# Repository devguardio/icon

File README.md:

ICON the internets RGB panel
-----------------------------

A  WIFI connected RGB panel you can directly program on your personal computer using javascript, golang, rust, C, C++, python, etc

Display stuff from afar without a cloud! The devguard carrier SDK allows direct peer to peer encrypted connection to the device over the internet.

Getting started
===============

1. Press the reset button to reset to factory settings
2. use the ESP Provision App to supply your wifi password
3. Scan the bardcode on your device to get the devguard carrier identity
4. run `carrier config auth <identity> auth add self "*"`
5. play with the example source code to display some pixels!

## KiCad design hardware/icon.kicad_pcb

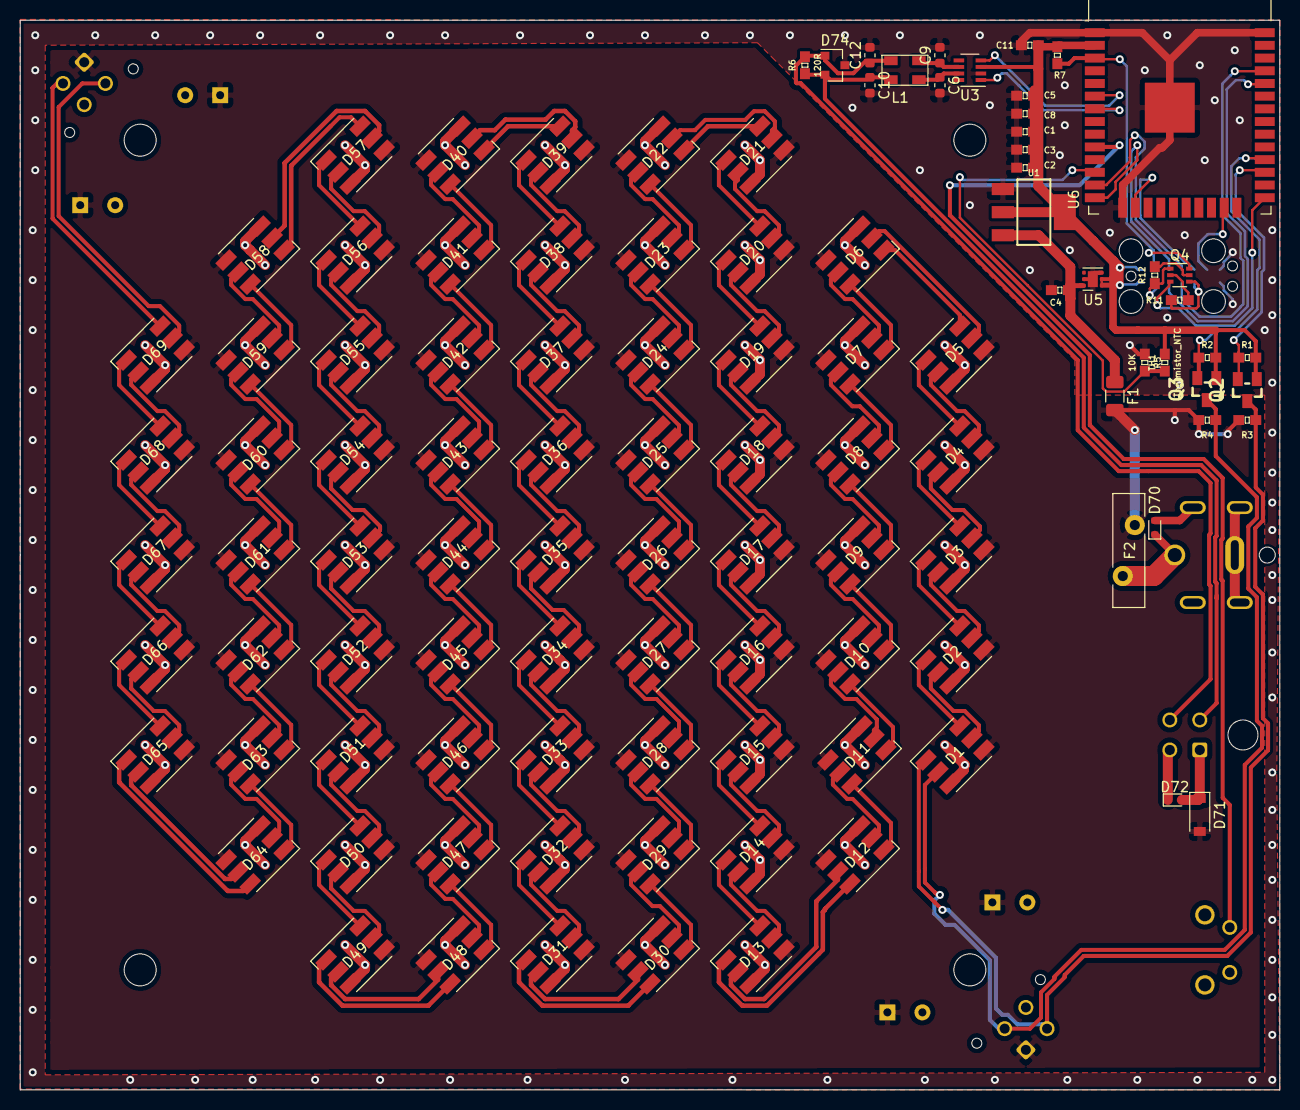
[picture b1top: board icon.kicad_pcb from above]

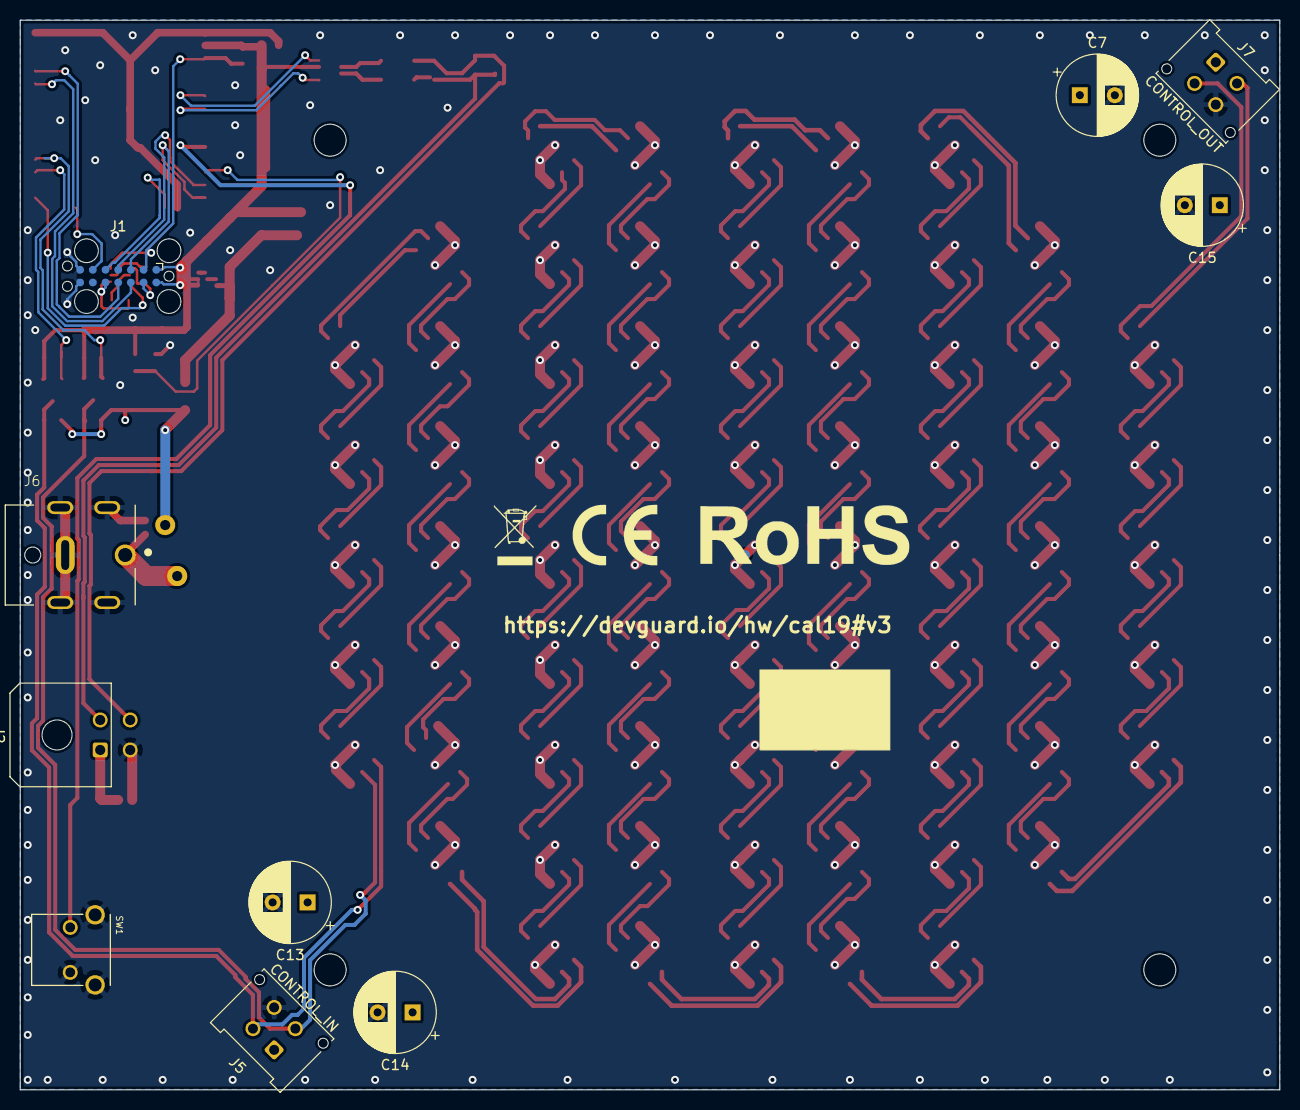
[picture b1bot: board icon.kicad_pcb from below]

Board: 2 copper layers, 126.0 x 107.0 mm, 122 parts (14 on the bottom side), 168 nets.

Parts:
C1, C2, C3, C5, C8, C11: 2.2uF; 0603
C4: 1uF; 0603
C6, C9, C10, C12: 56pf; C_0603_1608Metric
C7, C13, C14, C15: CP; CP_Radial_D8.0mm_P3.50mm
D1, D2, D3, D4, D5, D6, D7, D8, D9, D10, D11, D12, D13, D14, D15, D16, D17, D18, D19, D20, D21, D22, D23, D24, D25, D26, D27, D28, D29, D30, D31, D32, D33, D34, D35, D36, D37, D38, D39, D40, D41, D42, D43, D44, D45, D46, D47, D48, D49, D50, D51, D52, D53, D54, D55, D56, D57, D58, D59, D60, D61, D62, D63, D64, D65, D66, D67, D68, D69: APA102; LED_RGB_5050-6
D70: Transient Suppressor 7-8V clamp; D_SOD-523
D71: D_Schottky 3A; D_SOD-123
D72: Transient Suppressor; D_SOD-523
D74: SZNUP2105L; SOT-23
F1: PTC 0.5A; Fuse_1206_3216Metric
F2: 650-RGEF500; Fuse_Bourns_MF-RHT500
FID1: Fiducial; FIDUCIAL-1X2
H1, H2, H3, H4: MountingHole; MountingHole_3.2mm_M3
J1: UART; Tag-Connect_TC2070-IDC-FP_2x07_P1.27mm_Vertical
J2: Conn_02x02_Top_Bottom; Molex_Micro-Fit_3.0_43045-0400_2x02_P3.00mm_Horizontal
J5: CONTROL_IN; Molex_Micro-Fit_3.0_43045-0412_2x02_P3.00mm_Vertical
J6: PJ-082BH; CUI_PJ-082BH
J7: CONTROL_OUT; Molex_Micro-Fit_3.0_43045-0412_2x02_P3.00mm_Vertical
L1: PE-1210ACC110STS 11UH; PE-1210ACC
Q2, Q3: MOSFET-NCH-BSS138; SOT23-3
Q4: MBT3904DW1; SOT-363_SC-70-6
R1, R2, R3, R4, R5, R7, R11, R12: 10K; 0603
R6: 120R; 0603
SW1: SW_Push; SW_1825027-5
TH1: Thermistor_NTC; 0603
U1: AZ1117IH-3.3TRG; SOT223
U3: TCAN332; SOT-23-8
U5: 595-TLV76733DRVR; WSON-6-1EP_2x2mm_P0.65mm_EP1x1.6mm
U6: ESP32-WROOM-32D; ESP32-WROOM-32
X1: dummy; WEEE-Logo_4.2x6mm_SilkScreen
X2: dummy; RoHS-Logo_6mm_SilkScreen
X3: dummy; CE-Logo_8.5x6mm_SilkScreen

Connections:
5V: C7.1, C13.1, C14.1, C15.1, D1.4, D2.4, D3.4, D4.4, D5.4, D6.4, D7.4, D8.4, D9.4, D10.4, D11.4, D12.4, D13.4, D14.4, D15.4, D16.4, D17.4, D18.4, D19.4, D20.4, D21.4, D22.4, D23.4, D24.4, D25.4, D26.4, D27.4, D28.4, D29.4, D30.4, D31.4, D32.4, D33.4, D34.4, D35.4, D36.4, D37.4, D38.4, D39.4, D40.4, D41.4, D42.4, D43.4, D44.4, D45.4, D46.4, D47.4, D48.4, D49.4, D50.4, D51.4, D52.4, D53.4, D54.4, D55.4, D56.4, D57.4, D58.4, D59.4, D60.4, D61.4, D62.4, D63.4, D64.4, D65.4, D66.4, D67.4, D68.4, D69.4, D71.2, F1.2, F2.1, J5.1, J7.1, R3.2, R4.2
/c2+: C6.1, L1.2, U3.7
/c2-: C9.1, L1.1, U3.6
ADC_T: R5.2, TH1.1, U6.12
C0: D1.2, J5.3, Q3.3, R4.1
C1: D31.5, D32.2
CAN0+: C10.1, D74.2, J2.2, L1.3, R6.1
CAN0-: C12.1, D74.1, J2.4, L1.4, R6.2
CAN_RX: U3.4, U6.6
CAN_TX: U3.1, U6.7
CPU_BOOT: Q4.3, U6.25
CPU_ENABLE: J1.2, Q4.6, R7.1, U6.3
D0: D1.1, J5.2, Q2.3, R3.1
D1: D31.6, D32.1
FTDI_CTS: J1.13, Q4.1, R12.1
FTDI_DTR: J1.10, Q4.4, R11.1
FTDI_RXD: J1.11, U6.35
FTDI_TXD: J1.12, U6.34
GND: C1.2, C2.2, C3.2, C4.2, C5.2, C6.2, C7.2, C8.2, C9.2, C10.2, C11.2, C12.2, C13.2, C14.2, C15.2, D1.3, D2.3, D3.3, D4.3, D5.3, D6.3, D7.3, D8.3, D9.3, D10.3, D11.3, D12.3, D13.3, D14.3, D15.3, D16.3, D17.3, D18.3, D19.3, D20.3, D21.3, D22.3, D23.3, D24.3, D25.3, D26.3, D27.3, D28.3, D29.3, D30.3, D31.3, D32.3, D33.3, D34.3, D35.3, D36.3, D37.3, D38.3, D39.3, D40.3, D41.3, D42.3, D43.3, D44.3, D45.3, D46.3, D47.3, D48.3, D49.3, D50.3, D51.3, D52.3, D53.3, D54.3, D55.3, D56.3, D57.3, D58.3, D59.3, D60.3, D61.3, D62.3, D63.3, D64.3, D65.3, D66.3, D67.3, D68.3, D69.3, D70.2, D72.1, D74.3, J1.7, J1.8, J2.3, J5.4, J6.2, J6.3, J6.4, J6.5, J6.6, J7.4, R5.1, SW1.2, SW1.S1, SW1.S2, U1.1, U3.2, U5.3, U5.5, U5.7, U6.1, U6.15, U6.38, U6.39
JTAG_TCK: J1.5, U6.16
JTAG_TDI: J1.3, U6.14
JTAG_TDO: J1.6, U6.23
JTAG_TMS: J1.4, U6.13
LED_CLOCK: Q3.2, R2.1, U6.28
LED_DATA: Q2.2, R1.1, U6.27
unnamed: C4.1, F1.1, U1.3, U5.6
unnamed: D1.5, D2.2
unnamed: D1.6, D2.1
unnamed: D2.5, D3.2
unnamed: D2.6, D3.1
unnamed: D3.5, D4.2
unnamed: D3.6, D4.1
unnamed: D4.5, D5.2
unnamed: D4.6, D5.1
unnamed: D5.5, D6.2
unnamed: D5.6, D6.1
unnamed: D6.5, D7.2
unnamed: D6.6, D7.1
unnamed: D7.5, D8.2
unnamed: D7.6, D8.1
unnamed: D8.5, D9.2
unnamed: D8.6, D9.1
unnamed: D9.6, D10.1
unnamed: D9.5, D10.2
unnamed: D10.5, D11.2
unnamed: D10.6, D11.1
unnamed: D11.5, D12.2
unnamed: D11.6, D12.1
unnamed: D12.5, D13.2
unnamed: D12.6, D13.1
unnamed: D13.5, D14.2
unnamed: D13.6, D14.1
unnamed: D14.5, D15.2
unnamed: D14.6, D15.1
unnamed: D15.5, D16.2
unnamed: D15.6, D16.1
unnamed: D16.5, D17.2
unnamed: D16.6, D17.1
unnamed: D17.5, D18.2
unnamed: D17.6, D18.1
unnamed: D18.5, D19.2
unnamed: D18.6, D19.1
unnamed: D19.5, D20.2
unnamed: D19.6, D20.1
unnamed: D20.5, D21.2
unnamed: D20.6, D21.1
unnamed: D21.5, D22.2
unnamed: D21.6, D22.1
unnamed: D22.5, D23.2
unnamed: D22.6, D23.1
unnamed: D23.5, D24.2
unnamed: D23.6, D24.1
unnamed: D24.5, D25.2
unnamed: D24.6, D25.1
unnamed: D25.5, D26.2
unnamed: D25.6, D26.1
unnamed: D26.5, D27.2
unnamed: D26.6, D27.1
unnamed: D27.5, D28.2
unnamed: D27.6, D28.1
unnamed: D28.5, D29.2
unnamed: D28.6, D29.1
unnamed: D29.5, D30.2
unnamed: D29.6, D30.1
unnamed: D30.5, D31.2
unnamed: D30.6, D31.1
unnamed: D32.5, D33.2
unnamed: D32.6, D33.1
unnamed: D33.5, D34.2
unnamed: D33.6, D34.1
unnamed: D34.5, D35.2
unnamed: D34.6, D35.1
unnamed: D35.5, D36.2
unnamed: D35.6, D36.1
unnamed: D36.5, D37.2
unnamed: D36.6, D37.1
unnamed: D37.5, D38.2
unnamed: D37.6, D38.1
unnamed: D38.5, D39.2
unnamed: D38.6, D39.1
unnamed: D39.5, D40.2
unnamed: D39.6, D40.1
unnamed: D40.5, D41.2
unnamed: D40.6, D41.1
unnamed: D41.5, D42.2
unnamed: D41.6, D42.1
unnamed: D42.5, D43.2
unnamed: D42.6, D43.1
unnamed: D43.5, D44.2
unnamed: D43.6, D44.1
unnamed: D44.5, D45.2
unnamed: D44.6, D45.1
unnamed: D45.5, D46.2
unnamed: D45.6, D46.1
unnamed: D46.5, D47.2
unnamed: D46.6, D47.1
unnamed: D47.5, D48.2
unnamed: D47.6, D48.1
unnamed: D48.5, D49.2
unnamed: D48.6, D49.1
unnamed: D49.5, D50.2
unnamed: D49.6, D50.1
unnamed: D50.5, D51.2
unnamed: D50.6, D51.1
unnamed: D51.5, D52.2
unnamed: D51.6, D52.1
unnamed: D52.5, D53.2
unnamed: D52.6, D53.1
unnamed: D53.5, D54.2
unnamed: D53.6, D54.1
unnamed: D54.5, D55.2
unnamed: D54.6, D55.1
unnamed: D55.5, D56.2
unnamed: D55.6, D56.1
unnamed: D56.5, D57.2
unnamed: D56.6, D57.1
unnamed: D57.5, D58.2
unnamed: D57.6, D58.1
unnamed: D58.5, D59.2
unnamed: D58.6, D59.1
unnamed: D59.5, D60.2
unnamed: D59.6, D60.1
unnamed: D60.5, D61.2
unnamed: D60.6, D61.1
unnamed: D61.5, D62.2
unnamed: D61.6, D62.1
unnamed: D62.5, D63.2
unnamed: D62.6, D63.1
unnamed: D63.5, D64.2
unnamed: D63.6, D64.1
unnamed: D64.5, D65.2
unnamed: D64.6, D65.1
unnamed: D65.5, D66.2
unnamed: D65.6, D66.1
unnamed: D66.5, D67.2
unnamed: D66.6, D67.1
unnamed: D67.5, D68.2
unnamed: D67.6, D68.1
unnamed: D68.5, D69.2
unnamed: D68.6, D69.1
unnamed: D69.5, J7.3
unnamed: D69.6, J7.2
unnamed: D70.1, F2.2, J6.1
unnamed: D71.1, D72.2, J2.1
unnamed: Q4.2, R11.2
unnamed: Q4.5, R12.2
VDD: C1.1, C2.1, C3.1, C5.1, C8.1, C11.1, J1.1, J1.14, Q2.1, Q3.1, R1.2, R2.2, R7.2, TH1.2, U1.2, U1.4, U3.3, U5.1, U5.2, U6.2
softreset: SW1.1, U6.10
